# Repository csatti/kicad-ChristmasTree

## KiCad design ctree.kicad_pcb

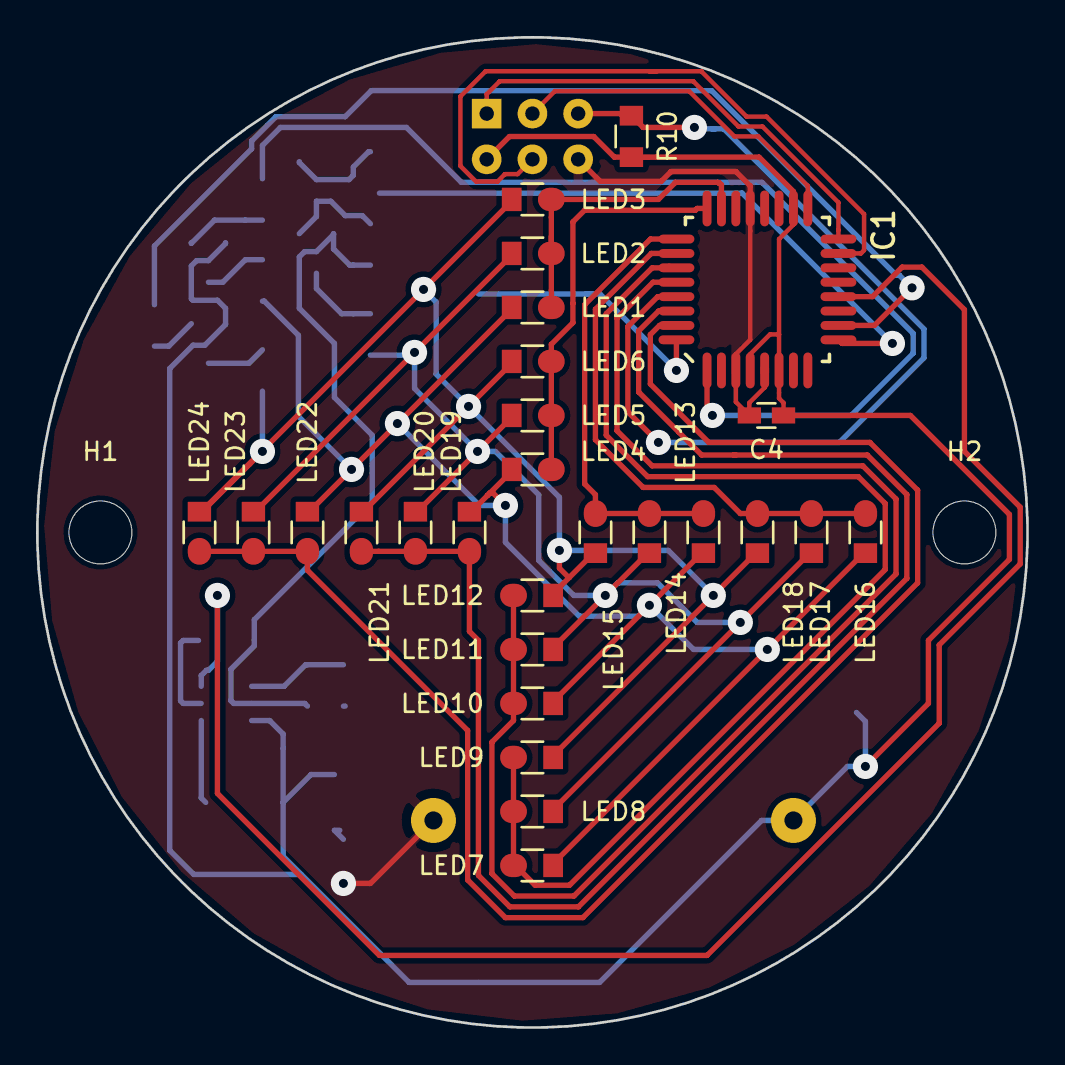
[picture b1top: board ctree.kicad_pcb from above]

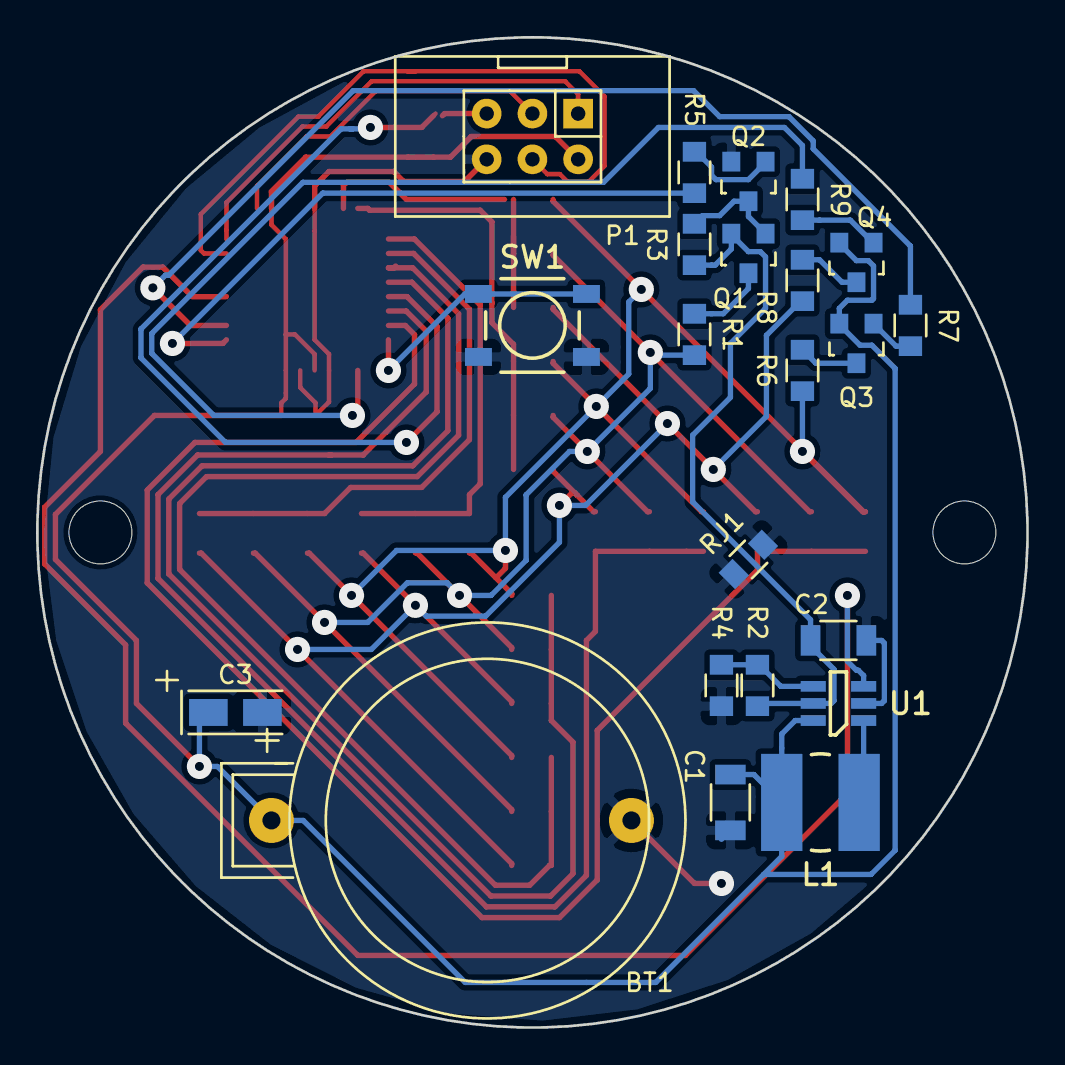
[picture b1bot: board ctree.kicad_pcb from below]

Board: 2 copper layers, 55.0 x 55.0 mm, 52 parts (23 on the bottom side), 32 nets.

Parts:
BT1: Battery; CR2032H_milling
C1: 1206_Unk4.7u25V; C_1206_milling
C2: CL31A106KOHNNNE; C_1206_milling
C3: NOJA226M006; TantalC_SizeA_EIA-3216_milling
C4: CL10B104KB8NNNC; C_0603_milling
H1, H2: MountingHole; MountingHole_3-5mm
H3: Logo
IC1: ATMEGA328P-A; TQFP-32_7x7mm_Pitch0.8mm__milling
L1: 4.7uH; l_choke_6x5.4_H4.5_CD54
LED1, LED2, LED3, LED4, LED5, LED6, LED7, LED8, LED9, LED10, LED11, LED12, LED13, LED14, LED15, LED16, LED17, LED18, LED19, LED20, LED21, LED22, LED23, LED24: Blue; LED_0805_milling
P1: CONN_02X03_PROG; ICSP_6Pin_IDC
Q1, Q3, Q4: IRLML6402; SOT-23_milling
Q2: BC817; SOT-23_milling
R1: 27; R_0805_milling
R2: 510k; R_0805_milling
R3, R5, R7, R9: 100k; R_0805_milling
R4: 300k; R_0805_milling
R6, R8: 39; R_0805_milling
R10: 10k; R_0805_milling
RJ1: R_Jumper; RJ_0805_milling
SW1: SMD_5.2x5.2; pbutton_5.2x5.2_H2
U1: MCP1624; SOT23-6L_milling

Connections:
+3V3: C2.1, Q1.2, R2.1, R3.1, U1.5
+BATT: BT1.1, C1.1, C3.1, C4.1, IC1.4, IC1.6, IC1.18, L1.1, P1.2, Q3.2, Q4.2, R10.1, U1.6
/BLUE: IC1.9, R5.1
/B_EN: IC1.12, U1.3
/GREEN: IC1.1, R9.1
/LED_C1: IC1.23, LED1.2, LED2.2, LED3.2
/LED_C2: IC1.24, LED4.2, LED5.2, LED6.2
/LED_C3: IC1.27, LED7.2, LED8.2, LED9.2
/LED_C4: IC1.28, LED10.2, LED11.2, LED12.2
/LED_C5: IC1.25, LED13.2, LED14.2, LED15.2
/LED_C6: IC1.26, LED16.2, LED17.2, LED18.2
/LED_C7: IC1.30, LED19.2, LED20.2, LED21.2
/LED_C8: IC1.31, LED22.2, LED23.2, LED24.2
/MISO: IC1.16, P1.1
/MOSI: IC1.15, P1.4
/PWR_BLUE: LED2.1, LED5.1, LED8.1, LED11.1, LED14.1, LED17.1, LED20.1, LED23.1, R1.2
/PWR_GREEN: LED1.1, LED4.1, LED7.1, LED10.1, LED13.1, LED16.1, LED19.1, LED22.1, R8.2
/PWR_RED: LED3.1, LED6.1, LED9.1, LED12.1, LED15.1, LED18.1, LED21.1, LED24.1, R6.2
/RED: IC1.10, R7.1
/RESET: IC1.29, P1.5, R10.2
/SCK: IC1.17, P1.3
/SW: IC1.32, SW1.1
GND: BT1.2, C1.2, C2.2, C3.2, C4.2, IC1.3, IC1.5, IC1.21, P1.6, Q2.2, R4.2, RJ1.1, SW1.2, U1.2
unnamed: L1.2, U1.1
unnamed: Q1.1, Q2.3, R3.2
unnamed: Q1.3, R1.1
unnamed: Q2.1, R5.2
unnamed: Q3.1, R7.2
unnamed: Q3.3, R6.1
unnamed: Q4.1, R9.2
unnamed: Q4.3, R8.1
unnamed: R2.2, R4.1, U1.4

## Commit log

2015-12-09 Work on schematic.
2015-12-10 Removed 12 additional LEDs. 24 LEDs are enough for such a small current project.
2015-12-11 Some changes for the schematics. Start of work on PCB.
2015-12-11 PCB ready for fabrication.
2015-12-11 Fabrication.
2015-12-12 Mask settings.
2015-12-12 Replaced BC817 with BC848 transistor.
